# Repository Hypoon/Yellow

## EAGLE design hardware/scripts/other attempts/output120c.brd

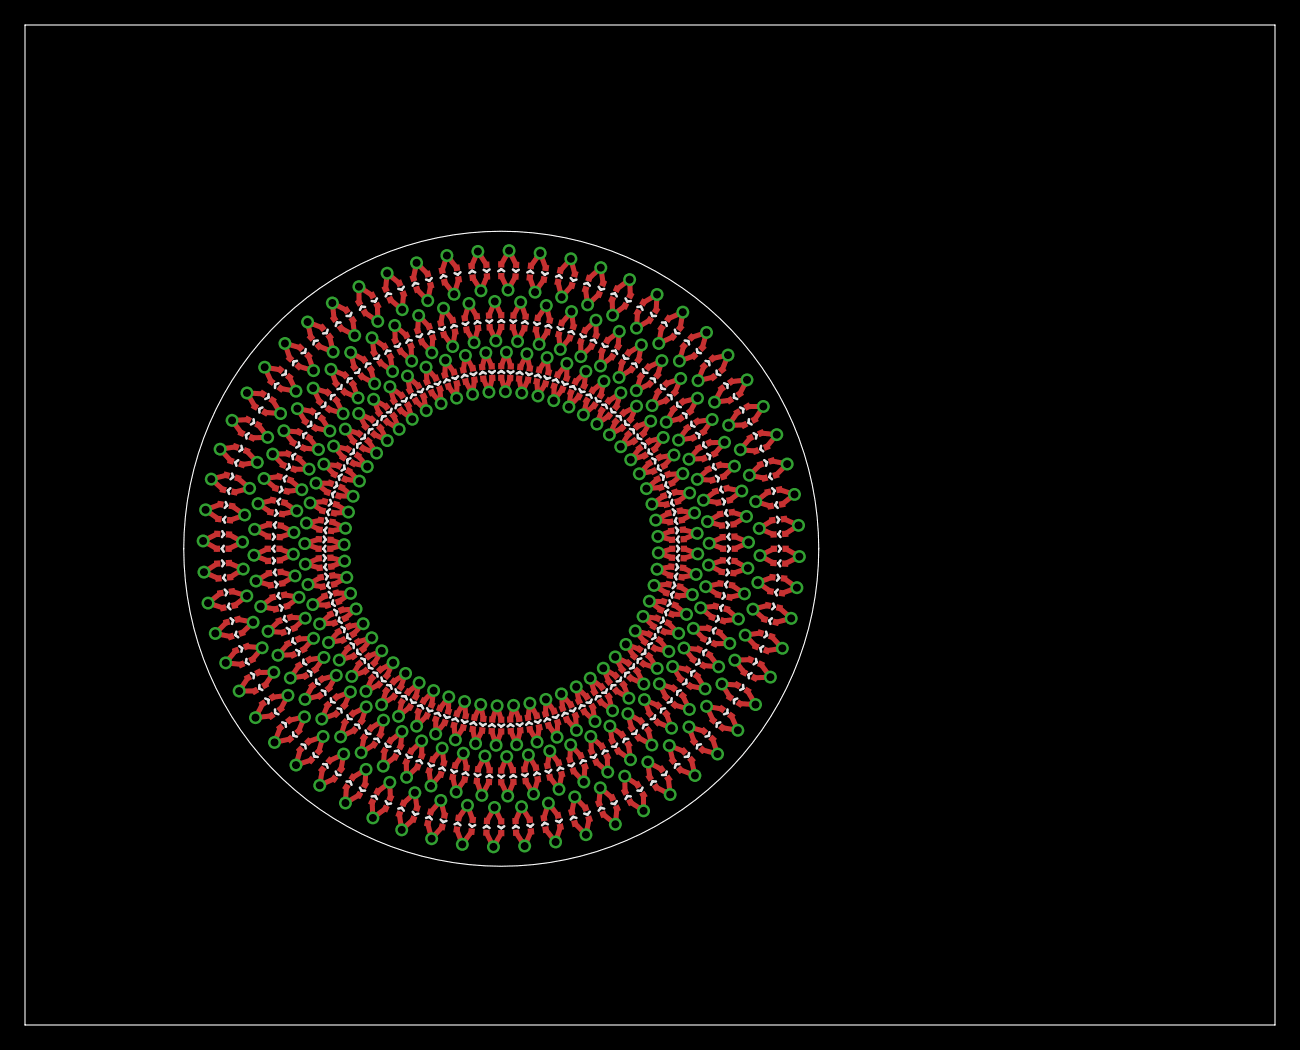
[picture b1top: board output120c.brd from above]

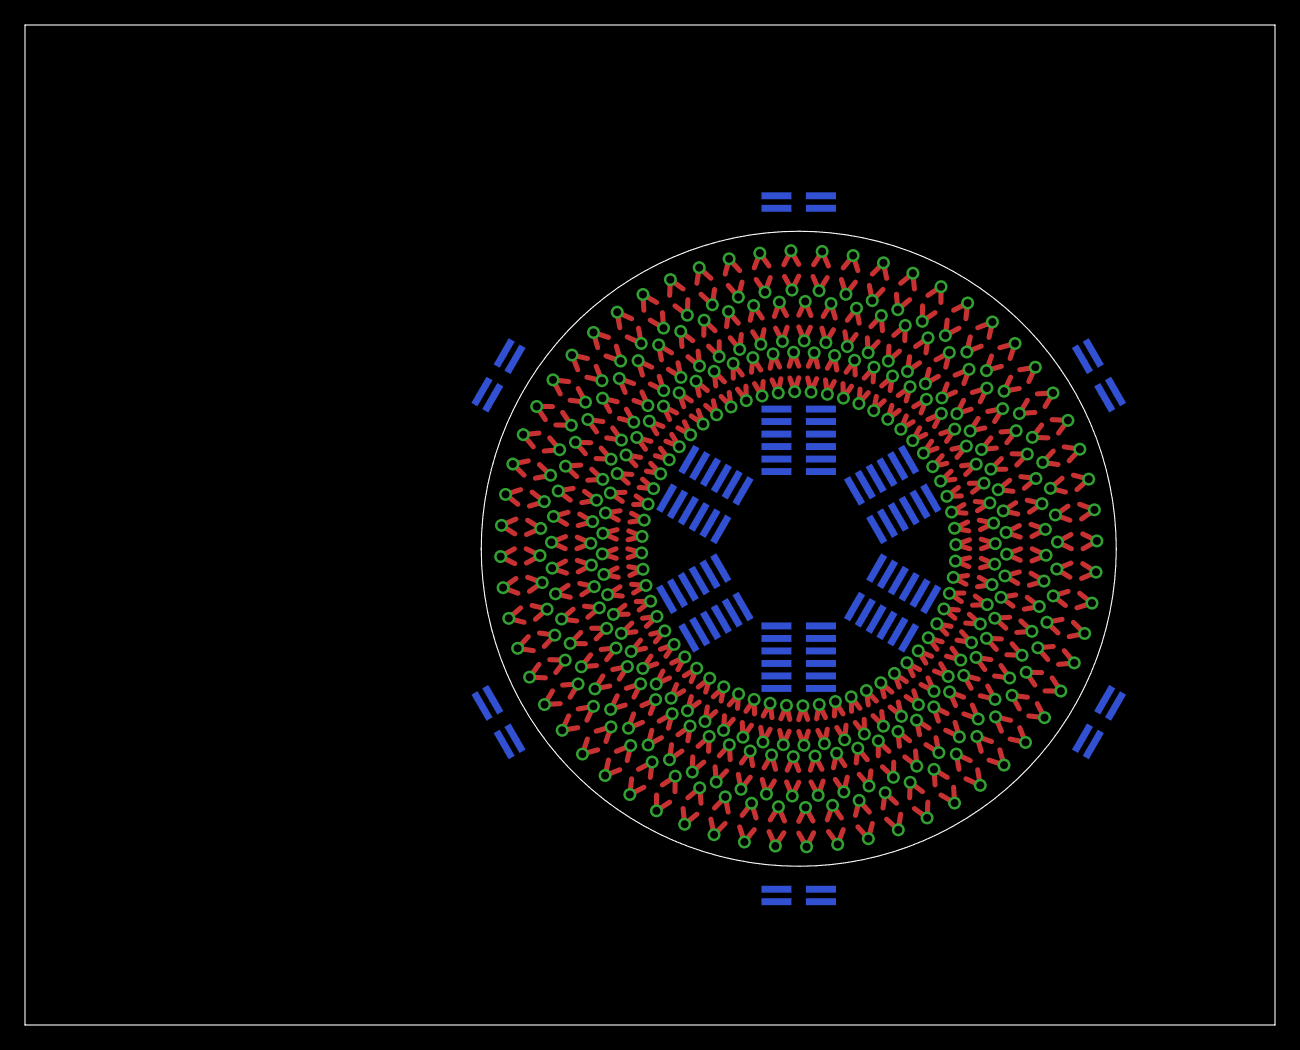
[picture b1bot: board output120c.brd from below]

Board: 2 copper layers, 100.0 x 80.0 mm, 378 parts (18 on the bottom side), 360 nets.

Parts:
H1, H2, H3, H4, H5, H6, H7, H8, H9, H10, H11, H12: 2X3; 3X2_1MM_SMD
H13, H14, H15, H16, H17, H18: 2X2; 2X2_1MM_SMD
LED1, LED2, LED3, LED4, LED5, LED6, LED7, LED8, LED9, LED10, LED11, LED12, LED13, LED14, LED15, LED16, LED17, LED18, LED19, LED20, LED21, LED22, LED23, LED24, LED25, LED26, LED27, LED28, LED29, LED30, LED31, LED32, LED33, LED34, LED35, LED36, LED37, LED38, LED39, LED40, LED41, LED42, LED43, LED44, LED45, LED46, LED47, LED48, LED49, LED50, LED51, LED52, LED53, LED54, LED55, LED56, LED57, LED58, LED59, LED60, LED61, LED62, LED63, LED64, LED65, LED66, LED67, LED68, LED69, LED70, LED71, LED72, LED73, LED74, LED75, LED76, LED77, LED78, LED79, LED80, LED81, LED82, LED83, LED84, LED85, LED86, LED87, LED88, LED89, LED90, LED91, LED92, LED93, LED94, LED95, LED96, LED97, LED98, LED99, LED100, LED101, LED102, LED103, LED104, LED105, LED106, LED107, LED108, LED109, LED110, LED111, LED112, LED113, LED114, LED115, LED116, LED117, LED118, LED119, LED120: RED; LED-0402
LED121, LED122, LED123, LED124, LED125, LED126, LED127, LED128, LED129, LED130, LED131, LED132, LED133, LED134, LED135, LED136, LED137, LED138, LED139, LED140, LED141, LED142, LED143, LED144, LED145, LED146, LED147, LED148, LED149, LED150, LED151, LED152, LED153, LED154, LED155, LED156, LED157, LED158, LED159, LED160, LED161, LED162, LED163, LED164, LED165, LED166, LED167, LED168, LED169, LED170, LED171, LED172, LED173, LED174, LED175, LED176, LED177, LED178, LED179, LED180, LED181, LED182, LED183, LED184, LED185, LED186, LED187, LED188, LED189, LED190, LED191, LED192, LED193, LED194, LED195, LED196, LED197, LED198, LED199, LED200, LED201, LED202, LED203, LED204, LED205, LED206, LED207, LED208, LED209, LED210, LED211, LED212, LED213, LED214, LED215, LED216, LED217, LED218, LED219, LED220, LED221, LED222, LED223, LED224, LED225, LED226, LED227, LED228, LED229, LED230, LED231, LED232, LED233, LED234, LED235, LED236, LED237, LED238, LED239, LED240: GREEN; LED-0402
LED241, LED242, LED243, LED244, LED245, LED246, LED247, LED248, LED249, LED250, LED251, LED252, LED253, LED254, LED255, LED256, LED257, LED258, LED259, LED260, LED261, LED262, LED263, LED264, LED265, LED266, LED267, LED268, LED269, LED270, LED271, LED272, LED273, LED274, LED275, LED276, LED277, LED278, LED279, LED280, LED281, LED282, LED283, LED284, LED285, LED286, LED287, LED288, LED289, LED290, LED291, LED292, LED293, LED294, LED295, LED296, LED297, LED298, LED299, LED300, LED301, LED302, LED303, LED304, LED305, LED306, LED307, LED308, LED309, LED310, LED311, LED312, LED313, LED314, LED315, LED316, LED317, LED318, LED319, LED320, LED321, LED322, LED323, LED324, LED325, LED326, LED327, LED328, LED329, LED330, LED331, LED332, LED333, LED334, LED335, LED336, LED337, LED338, LED339, LED340, LED341, LED342, LED343, LED344, LED345, LED346, LED347, LED348, LED349, LED350, LED351, LED352, LED353, LED354, LED355, LED356, LED357, LED358, LED359, LED360: BLUE; LED-0402

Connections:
unnamed: LED1.A, LED2.C
unnamed: LED3.A, LED4.C
unnamed: LED5.A, LED6.C
unnamed: LED7.A, LED8.C
unnamed: LED9.A, LED10.C
unnamed: LED11.A, LED12.C
unnamed: LED13.A, LED14.C
unnamed: LED15.A, LED16.C
unnamed: LED17.A, LED18.C
unnamed: LED19.A, LED20.C
unnamed: LED21.A, LED22.C
unnamed: LED23.A, LED24.C
unnamed: LED25.A, LED26.C
unnamed: LED27.A, LED28.C
unnamed: LED29.A, LED30.C
unnamed: LED31.A, LED32.C
unnamed: LED33.A, LED34.C
unnamed: LED35.A, LED36.C
unnamed: LED37.A, LED38.C
unnamed: LED39.A, LED40.C
unnamed: LED41.A, LED42.C
unnamed: LED43.A, LED44.C
unnamed: LED45.A, LED46.C
unnamed: LED47.A, LED48.C
unnamed: LED49.A, LED50.C
unnamed: LED51.A, LED52.C
unnamed: LED53.A, LED54.C
unnamed: LED55.A, LED56.C
unnamed: LED57.A, LED58.C
unnamed: LED59.A, LED60.C
unnamed: LED61.A, LED62.C
unnamed: LED63.A, LED64.C
unnamed: LED65.A, LED66.C
unnamed: LED67.A, LED68.C
unnamed: LED69.A, LED70.C
unnamed: LED71.A, LED72.C
unnamed: LED73.A, LED74.C
unnamed: LED75.A, LED76.C
unnamed: LED77.A, LED78.C
unnamed: LED79.A, LED80.C
unnamed: LED81.A, LED82.C
unnamed: LED83.A, LED84.C
unnamed: LED85.A, LED86.C
unnamed: LED87.A, LED88.C
unnamed: LED89.A, LED90.C
unnamed: LED91.A, LED92.C
unnamed: LED93.A, LED94.C
unnamed: LED95.A, LED96.C
unnamed: LED97.A, LED98.C
unnamed: LED99.A, LED100.C
unnamed: LED101.A, LED102.C
unnamed: LED103.A, LED104.C
unnamed: LED105.A, LED106.C
unnamed: LED107.A, LED108.C
unnamed: LED109.A, LED110.C
unnamed: LED111.A, LED112.C
unnamed: LED113.A, LED114.C
unnamed: LED115.A, LED116.C
unnamed: LED117.A, LED118.C
unnamed: LED119.A, LED120.C
unnamed: LED122.C, LED123.A
unnamed: LED124.C, LED125.A
unnamed: LED126.C, LED127.A
unnamed: LED128.C, LED129.A
unnamed: LED130.C, LED131.A
unnamed: LED132.C, LED133.A
unnamed: LED134.C, LED135.A
unnamed: LED136.C, LED137.A
unnamed: LED138.C, LED139.A
unnamed: LED140.C, LED141.A
unnamed: LED142.C, LED143.A
unnamed: LED144.C, LED145.A
unnamed: LED146.C, LED147.A
unnamed: LED148.C, LED149.A
unnamed: LED150.C, LED151.A
unnamed: LED152.C, LED153.A
unnamed: LED154.C, LED155.A
unnamed: LED156.C, LED157.A
unnamed: LED158.C, LED159.A
unnamed: LED160.C, LED161.A
unnamed: LED162.C, LED163.A
unnamed: LED164.C, LED165.A
unnamed: LED166.C, LED167.A
unnamed: LED168.C, LED169.A
unnamed: LED170.C, LED171.A
unnamed: LED172.C, LED173.A
unnamed: LED174.C, LED175.A
unnamed: LED176.C, LED177.A
unnamed: LED178.C, LED179.A
unnamed: LED180.C, LED181.A
unnamed: LED182.C, LED183.A
unnamed: LED184.C, LED185.A
unnamed: LED186.C, LED187.A
unnamed: LED188.C, LED189.A
unnamed: LED190.C, LED191.A
unnamed: LED192.C, LED193.A
unnamed: LED194.C, LED195.A
unnamed: LED196.C, LED197.A
unnamed: LED198.C, LED199.A
unnamed: LED200.C, LED201.A
unnamed: LED202.C, LED203.A
unnamed: LED204.C, LED205.A
unnamed: LED206.C, LED207.A
unnamed: LED208.C, LED209.A
unnamed: LED210.C, LED211.A
unnamed: LED212.C, LED213.A
unnamed: LED214.C, LED215.A
unnamed: LED216.C, LED217.A
unnamed: LED218.C, LED219.A
unnamed: LED220.C, LED221.A
unnamed: LED222.C, LED223.A
unnamed: LED224.C, LED225.A
unnamed: LED226.C, LED227.A
unnamed: LED228.C, LED229.A
unnamed: LED230.C, LED231.A
unnamed: LED232.C, LED233.A
unnamed: LED234.C, LED235.A
unnamed: LED236.C, LED237.A
unnamed: LED238.C, LED239.A
unnamed: LED121.A, LED240.C
unnamed: LED241.A, LED242.C
unnamed: LED243.A, LED244.C
unnamed: LED245.A, LED246.C
unnamed: LED247.A, LED248.C
unnamed: LED249.A, LED250.C
unnamed: LED251.A, LED252.C
unnamed: LED253.A, LED254.C
unnamed: LED255.A, LED256.C
unnamed: LED257.A, LED258.C
unnamed: LED259.A, LED260.C
unnamed: LED261.A, LED262.C
unnamed: LED263.A, LED264.C
unnamed: LED265.A, LED266.C
unnamed: LED267.A, LED268.C
unnamed: LED269.A, LED270.C
unnamed: LED271.A, LED272.C
unnamed: LED273.A, LED274.C
unnamed: LED275.A, LED276.C
unnamed: LED277.A, LED278.C
unnamed: LED279.A, LED280.C
unnamed: LED281.A, LED282.C
unnamed: LED283.A, LED284.C
unnamed: LED285.A, LED286.C
unnamed: LED287.A, LED288.C
unnamed: LED289.A, LED290.C
unnamed: LED291.A, LED292.C
unnamed: LED293.A, LED294.C
unnamed: LED295.A, LED296.C
unnamed: LED297.A, LED298.C
unnamed: LED299.A, LED300.C
unnamed: LED301.A, LED302.C
unnamed: LED303.A, LED304.C
unnamed: LED305.A, LED306.C
unnamed: LED307.A, LED308.C
unnamed: LED309.A, LED310.C
unnamed: LED311.A, LED312.C
unnamed: LED313.A, LED314.C
unnamed: LED315.A, LED316.C
unnamed: LED317.A, LED318.C
unnamed: LED319.A, LED320.C
unnamed: LED321.A, LED322.C
unnamed: LED323.A, LED324.C
unnamed: LED325.A, LED326.C
unnamed: LED327.A, LED328.C
unnamed: LED329.A, LED330.C
unnamed: LED331.A, LED332.C
unnamed: LED333.A, LED334.C
unnamed: LED335.A, LED336.C
unnamed: LED337.A, LED338.C
unnamed: LED339.A, LED340.C
unnamed: LED341.A, LED342.C
unnamed: LED343.A, LED344.C
unnamed: LED345.A, LED346.C
unnamed: LED347.A, LED348.C
unnamed: LED349.A, LED350.C
unnamed: LED351.A, LED352.C
unnamed: LED353.A, LED354.C
unnamed: LED355.A, LED356.C
unnamed: LED357.A, LED358.C
unnamed: LED359.A, LED360.C
unnamed: LED1.C, LED2.A
unnamed: LED3.C, LED4.A
unnamed: LED5.C, LED6.A
unnamed: LED7.C, LED8.A
unnamed: LED9.C, LED10.A
unnamed: LED11.C, LED12.A
unnamed: LED13.C, LED14.A
unnamed: LED15.C, LED16.A
unnamed: LED17.C, LED18.A
unnamed: LED19.C, LED20.A
unnamed: LED21.C, LED22.A
unnamed: LED23.C, LED24.A
unnamed: LED25.C, LED26.A
unnamed: LED27.C, LED28.A
unnamed: LED29.C, LED30.A
unnamed: LED31.C, LED32.A
unnamed: LED33.C, LED34.A
unnamed: LED35.C, LED36.A
unnamed: LED37.C, LED38.A
unnamed: LED39.C, LED40.A
unnamed: LED41.C, LED42.A
unnamed: LED43.C, LED44.A
unnamed: LED45.C, LED46.A
unnamed: LED47.C, LED48.A
unnamed: LED49.C, LED50.A
unnamed: LED51.C, LED52.A
unnamed: LED53.C, LED54.A
unnamed: LED55.C, LED56.A
unnamed: LED57.C, LED58.A
unnamed: LED59.C, LED60.A
unnamed: LED61.C, LED62.A
unnamed: LED63.C, LED64.A
unnamed: LED65.C, LED66.A
unnamed: LED67.C, LED68.A
unnamed: LED69.C, LED70.A
unnamed: LED71.C, LED72.A
unnamed: LED73.C, LED74.A
unnamed: LED75.C, LED76.A
unnamed: LED77.C, LED78.A
unnamed: LED79.C, LED80.A
unnamed: LED81.C, LED82.A
unnamed: LED83.C, LED84.A
unnamed: LED85.C, LED86.A
unnamed: LED87.C, LED88.A
unnamed: LED89.C, LED90.A
unnamed: LED91.C, LED92.A
unnamed: LED93.C, LED94.A
unnamed: LED95.C, LED96.A
unnamed: LED97.C, LED98.A
unnamed: LED99.C, LED100.A
unnamed: LED101.C, LED102.A
unnamed: LED103.C, LED104.A
unnamed: LED105.C, LED106.A
unnamed: LED107.C, LED108.A
unnamed: LED109.C, LED110.A
unnamed: LED111.C, LED112.A
unnamed: LED113.C, LED114.A
unnamed: LED115.C, LED116.A
unnamed: LED117.C, LED118.A
unnamed: LED119.C, LED120.A
unnamed: LED122.A, LED123.C
unnamed: LED124.A, LED125.C
unnamed: LED126.A, LED127.C
unnamed: LED128.A, LED129.C
unnamed: LED130.A, LED131.C
unnamed: LED132.A, LED133.C
unnamed: LED134.A, LED135.C
unnamed: LED136.A, LED137.C
unnamed: LED138.A, LED139.C
unnamed: LED140.A, LED141.C
unnamed: LED142.A, LED143.C
unnamed: LED144.A, LED145.C
unnamed: LED146.A, LED147.C
unnamed: LED148.A, LED149.C
unnamed: LED150.A, LED151.C
unnamed: LED152.A, LED153.C
unnamed: LED154.A, LED155.C
unnamed: LED156.A, LED157.C
unnamed: LED158.A, LED159.C
unnamed: LED160.A, LED161.C
unnamed: LED162.A, LED163.C
unnamed: LED164.A, LED165.C
unnamed: LED166.A, LED167.C
unnamed: LED168.A, LED169.C
unnamed: LED170.A, LED171.C
unnamed: LED172.A, LED173.C
unnamed: LED174.A, LED175.C
unnamed: LED176.A, LED177.C
unnamed: LED178.A, LED179.C
unnamed: LED180.A, LED181.C
unnamed: LED182.A, LED183.C
unnamed: LED184.A, LED185.C
unnamed: LED186.A, LED187.C
unnamed: LED188.A, LED189.C
unnamed: LED190.A, LED191.C
unnamed: LED192.A, LED193.C
unnamed: LED194.A, LED195.C
unnamed: LED196.A, LED197.C
unnamed: LED198.A, LED199.C
unnamed: LED200.A, LED201.C
unnamed: LED202.A, LED203.C
unnamed: LED204.A, LED205.C
unnamed: LED206.A, LED207.C
unnamed: LED208.A, LED209.C
unnamed: LED210.A, LED211.C
unnamed: LED212.A, LED213.C
unnamed: LED214.A, LED215.C
unnamed: LED216.A, LED217.C
unnamed: LED218.A, LED219.C
unnamed: LED220.A, LED221.C
unnamed: LED222.A, LED223.C
unnamed: LED224.A, LED225.C
unnamed: LED226.A, LED227.C
unnamed: LED228.A, LED229.C
unnamed: LED230.A, LED231.C
unnamed: LED232.A, LED233.C
unnamed: LED234.A, LED235.C
unnamed: LED236.A, LED237.C
unnamed: LED238.A, LED239.C
unnamed: LED121.C, LED240.A
unnamed: LED241.C, LED242.A
unnamed: LED243.C, LED244.A
unnamed: LED245.C, LED246.A
unnamed: LED247.C, LED248.A
unnamed: LED249.C, LED250.A
unnamed: LED251.C, LED252.A
unnamed: LED253.C, LED254.A
unnamed: LED255.C, LED256.A
unnamed: LED257.C, LED258.A
unnamed: LED259.C, LED260.A
unnamed: LED261.C, LED262.A
unnamed: LED263.C, LED264.A
unnamed: LED265.C, LED266.A
unnamed: LED267.C, LED268.A
unnamed: LED269.C, LED270.A
unnamed: LED271.C, LED272.A
unnamed: LED273.C, LED274.A
unnamed: LED275.C, LED276.A
unnamed: LED277.C, LED278.A
unnamed: LED279.C, LED280.A
unnamed: LED281.C, LED282.A
unnamed: LED283.C, LED284.A
unnamed: LED285.C, LED286.A
unnamed: LED287.C, LED288.A
unnamed: LED289.C, LED290.A
unnamed: LED291.C, LED292.A
unnamed: LED293.C, LED294.A
unnamed: LED295.C, LED296.A
unnamed: LED297.C, LED298.A
unnamed: LED299.C, LED300.A
unnamed: LED301.C, LED302.A
unnamed: LED303.C, LED304.A
unnamed: LED305.C, LED306.A
unnamed: LED307.C, LED308.A
unnamed: LED309.C, LED310.A
unnamed: LED311.C, LED312.A
unnamed: LED313.C, LED314.A
unnamed: LED315.C, LED316.A
unnamed: LED317.C, LED318.A
unnamed: LED319.C, LED320.A
unnamed: LED321.C, LED322.A
unnamed: LED323.C, LED324.A
unnamed: LED325.C, LED326.A
unnamed: LED327.C, LED328.A
unnamed: LED329.C, LED330.A
unnamed: LED331.C, LED332.A
unnamed: LED333.C, LED334.A
unnamed: LED335.C, LED336.A
unnamed: LED337.C, LED338.A
unnamed: LED339.C, LED340.A
unnamed: LED341.C, LED342.A
unnamed: LED343.C, LED344.A
unnamed: LED345.C, LED346.A
unnamed: LED347.C, LED348.A
unnamed: LED349.C, LED350.A
unnamed: LED351.C, LED352.A
unnamed: LED353.C, LED354.A
unnamed: LED355.C, LED356.A
unnamed: LED357.C, LED358.A
unnamed: LED359.C, LED360.A

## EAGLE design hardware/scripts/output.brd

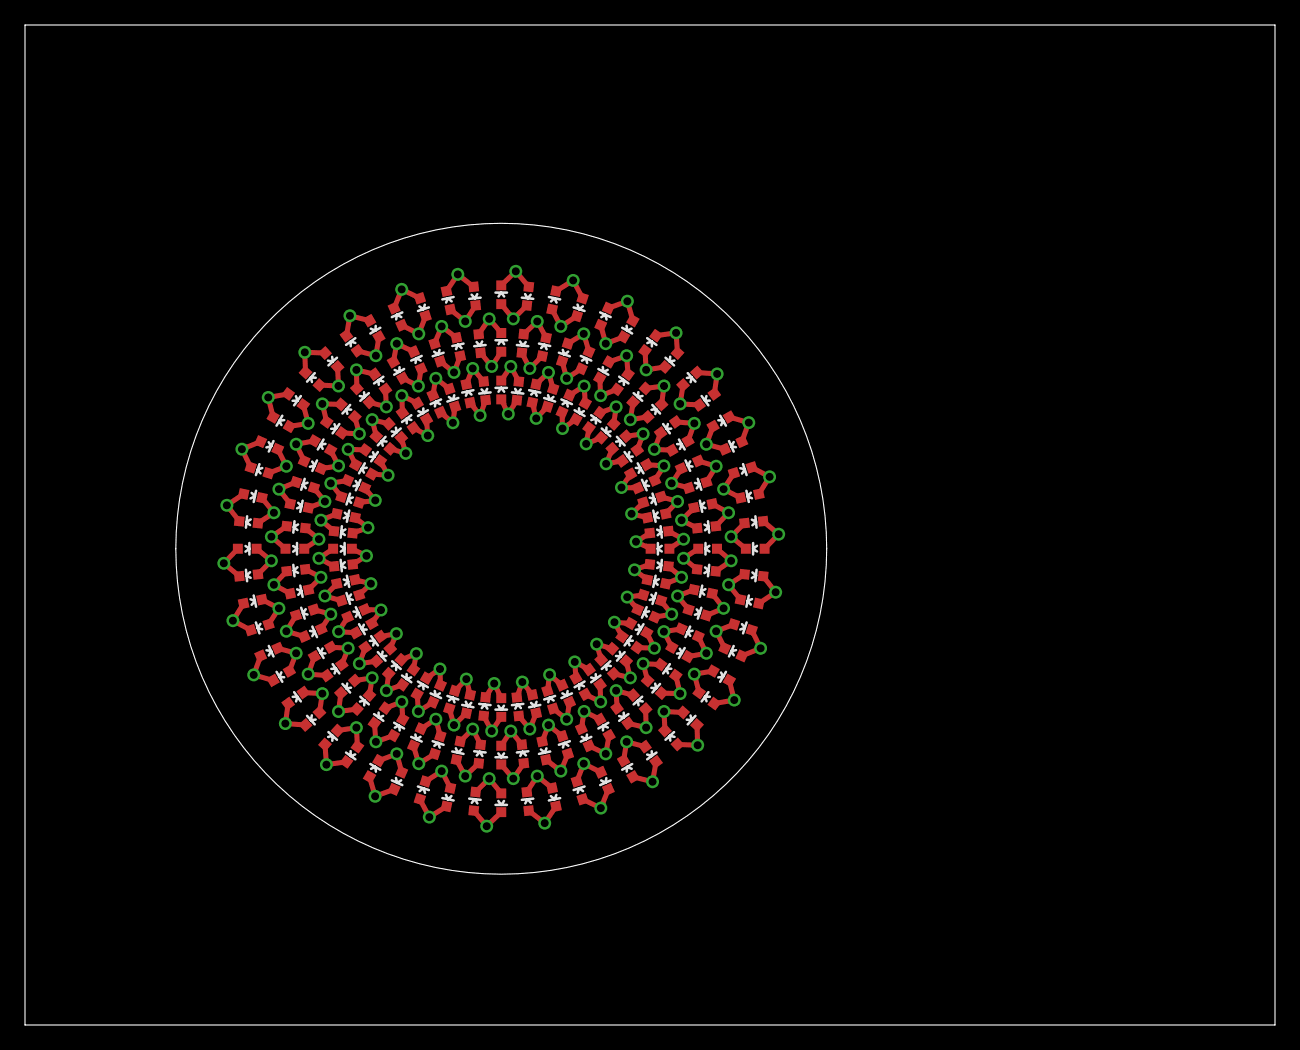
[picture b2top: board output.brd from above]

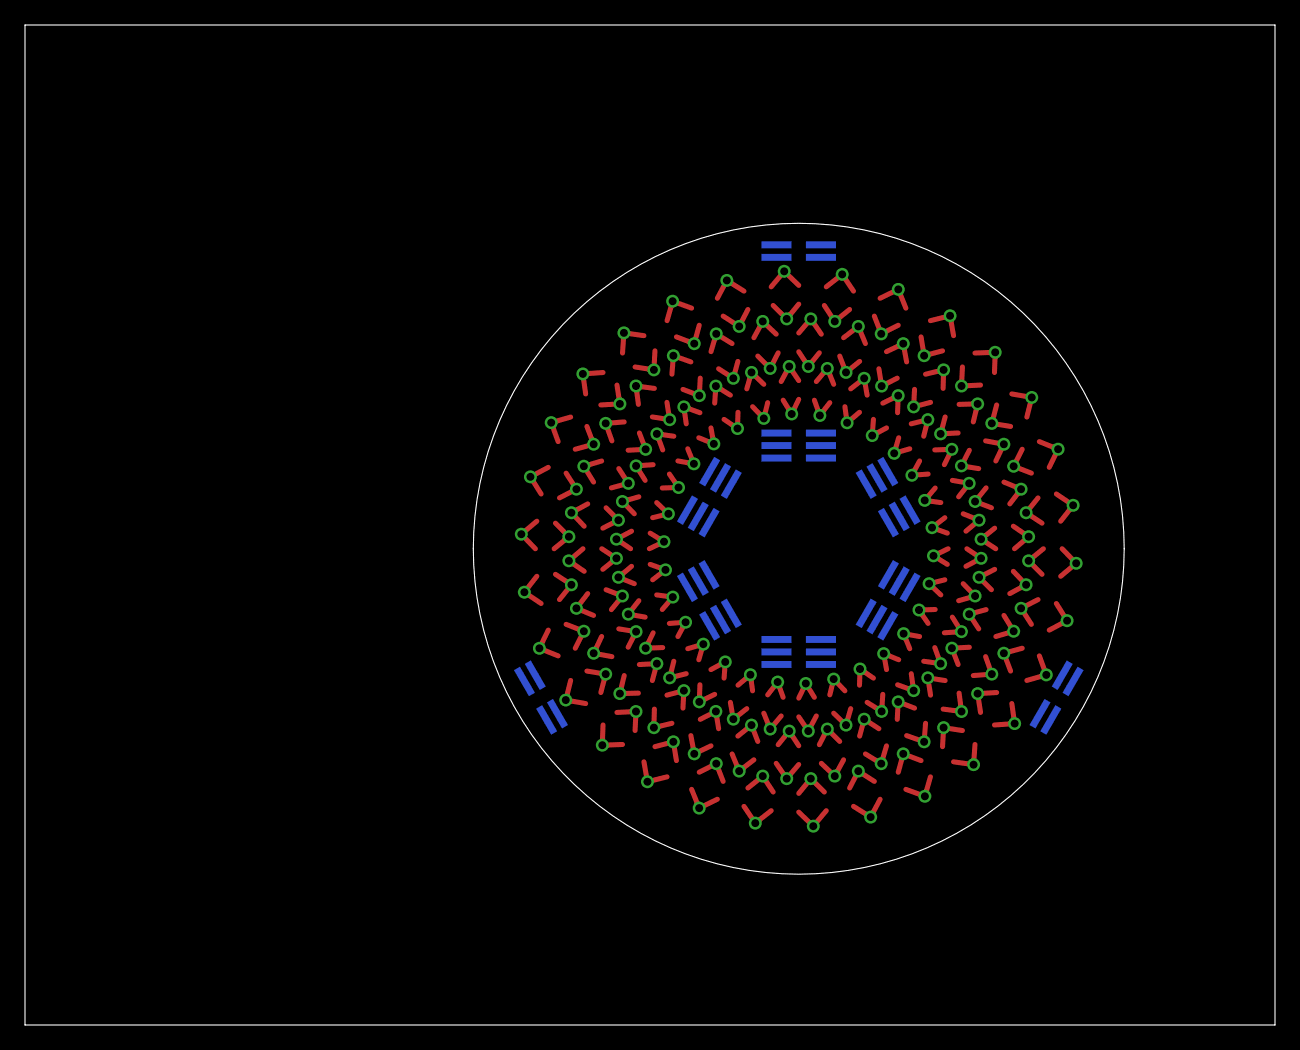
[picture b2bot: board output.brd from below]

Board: 2 copper layers, 100.0 x 80.0 mm, 189 parts (9 on the bottom side), 180 nets.

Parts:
H1, H2, H3, H4, H5, H6: 2X3; 3X2_1MM_SMD
H7, H8, H9: 2X2; 2X2_1MM_SMD
LED1, LED2, LED3, LED4, LED5, LED6, LED7, LED8, LED9, LED10, LED11, LED12, LED13, LED14, LED15, LED16, LED17, LED18, LED19, LED20, LED21, LED22, LED23, LED24, LED25, LED26, LED27, LED28, LED29, LED30, LED31, LED32, LED33, LED34, LED35, LED36, LED37, LED38, LED39, LED40, LED41, LED42, LED43, LED44, LED45, LED46, LED47, LED48, LED49, LED50, LED51, LED52, LED53, LED54, LED55, LED56, LED57, LED58, LED59, LED60: RED; LED-0603
LED61, LED62, LED63, LED64, LED65, LED66, LED67, LED68, LED69, LED70, LED71, LED72, LED73, LED74, LED75, LED76, LED77, LED78, LED79, LED80, LED81, LED82, LED83, LED84, LED85, LED86, LED87, LED88, LED89, LED90, LED91, LED92, LED93, LED94, LED95, LED96, LED97, LED98, LED99, LED100, LED101, LED102, LED103, LED104, LED105, LED106, LED107, LED108, LED109, LED110, LED111, LED112, LED113, LED114, LED115, LED116, LED117, LED118, LED119, LED120: GREEN; LED-0603
LED121, LED122, LED123, LED124, LED125, LED126, LED127, LED128, LED129, LED130, LED131, LED132, LED133, LED134, LED135, LED136, LED137, LED138, LED139, LED140, LED141, LED142, LED143, LED144, LED145, LED146, LED147, LED148, LED149, LED150, LED151, LED152, LED153, LED154, LED155, LED156, LED157, LED158, LED159, LED160, LED161, LED162, LED163, LED164, LED165, LED166, LED167, LED168, LED169, LED170, LED171, LED172, LED173, LED174, LED175, LED176, LED177, LED178, LED179, LED180: BLUE; LED-0603

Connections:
unnamed: LED1.A, LED2.C
unnamed: LED3.A, LED4.C
unnamed: LED5.A, LED6.C
unnamed: LED7.A, LED8.C
unnamed: LED9.A, LED10.C
unnamed: LED11.A, LED12.C
unnamed: LED13.A, LED14.C
unnamed: LED15.A, LED16.C
unnamed: LED17.A, LED18.C
unnamed: LED19.A, LED20.C
unnamed: LED21.A, LED22.C
unnamed: LED23.A, LED24.C
unnamed: LED25.A, LED26.C
unnamed: LED27.A, LED28.C
unnamed: LED29.A, LED30.C
unnamed: LED31.A, LED32.C
unnamed: LED33.A, LED34.C
unnamed: LED35.A, LED36.C
unnamed: LED37.A, LED38.C
unnamed: LED39.A, LED40.C
unnamed: LED41.A, LED42.C
unnamed: LED43.A, LED44.C
unnamed: LED45.A, LED46.C
unnamed: LED47.A, LED48.C
unnamed: LED49.A, LED50.C
unnamed: LED51.A, LED52.C
unnamed: LED53.A, LED54.C
unnamed: LED55.A, LED56.C
unnamed: LED57.A, LED58.C
unnamed: LED59.A, LED60.C
unnamed: LED62.C, LED63.A
unnamed: LED64.C, LED65.A
unnamed: LED66.C, LED67.A
unnamed: LED68.C, LED69.A
unnamed: LED70.C, LED71.A
unnamed: LED72.C, LED73.A
unnamed: LED74.C, LED75.A
unnamed: LED76.C, LED77.A
unnamed: LED78.C, LED79.A
unnamed: LED80.C, LED81.A
unnamed: LED82.C, LED83.A
unnamed: LED84.C, LED85.A
unnamed: LED86.C, LED87.A
unnamed: LED88.C, LED89.A
unnamed: LED90.C, LED91.A
unnamed: LED92.C, LED93.A
unnamed: LED94.C, LED95.A
unnamed: LED96.C, LED97.A
unnamed: LED98.C, LED99.A
unnamed: LED100.C, LED101.A
unnamed: LED102.C, LED103.A
unnamed: LED104.C, LED105.A
unnamed: LED106.C, LED107.A
unnamed: LED108.C, LED109.A
unnamed: LED110.C, LED111.A
unnamed: LED112.C, LED113.A
unnamed: LED114.C, LED115.A
unnamed: LED116.C, LED117.A
unnamed: LED118.C, LED119.A
unnamed: LED61.A, LED120.C
unnamed: LED121.A, LED122.C
unnamed: LED123.A, LED124.C
unnamed: LED125.A, LED126.C
unnamed: LED127.A, LED128.C
unnamed: LED129.A, LED130.C
unnamed: LED131.A, LED132.C
unnamed: LED133.A, LED134.C
unnamed: LED135.A, LED136.C
unnamed: LED137.A, LED138.C
unnamed: LED139.A, LED140.C
unnamed: LED141.A, LED142.C
unnamed: LED143.A, LED144.C
unnamed: LED145.A, LED146.C
unnamed: LED147.A, LED148.C
unnamed: LED149.A, LED150.C
unnamed: LED151.A, LED152.C
unnamed: LED153.A, LED154.C
unnamed: LED155.A, LED156.C
unnamed: LED157.A, LED158.C
unnamed: LED159.A, LED160.C
unnamed: LED161.A, LED162.C
unnamed: LED163.A, LED164.C
unnamed: LED165.A, LED166.C
unnamed: LED167.A, LED168.C
unnamed: LED169.A, LED170.C
unnamed: LED171.A, LED172.C
unnamed: LED173.A, LED174.C
unnamed: LED175.A, LED176.C
unnamed: LED177.A, LED178.C
unnamed: LED179.A, LED180.C
unnamed: LED1.C, LED2.A
unnamed: LED3.C, LED4.A
unnamed: LED5.C, LED6.A
unnamed: LED7.C, LED8.A
unnamed: LED9.C, LED10.A
unnamed: LED11.C, LED12.A
unnamed: LED13.C, LED14.A
unnamed: LED15.C, LED16.A
unnamed: LED17.C, LED18.A
unnamed: LED19.C, LED20.A
unnamed: LED21.C, LED22.A
unnamed: LED23.C, LED24.A
unnamed: LED25.C, LED26.A
unnamed: LED27.C, LED28.A
unnamed: LED29.C, LED30.A
unnamed: LED31.C, LED32.A
unnamed: LED33.C, LED34.A
unnamed: LED35.C, LED36.A
unnamed: LED37.C, LED38.A
unnamed: LED39.C, LED40.A
unnamed: LED41.C, LED42.A
unnamed: LED43.C, LED44.A
unnamed: LED45.C, LED46.A
unnamed: LED47.C, LED48.A
unnamed: LED49.C, LED50.A
unnamed: LED51.C, LED52.A
unnamed: LED53.C, LED54.A
unnamed: LED55.C, LED56.A
unnamed: LED57.C, LED58.A
unnamed: LED59.C, LED60.A
unnamed: LED62.A, LED63.C
unnamed: LED64.A, LED65.C
unnamed: LED66.A, LED67.C
unnamed: LED68.A, LED69.C
unnamed: LED70.A, LED71.C
unnamed: LED72.A, LED73.C
unnamed: LED74.A, LED75.C
unnamed: LED76.A, LED77.C
unnamed: LED78.A, LED79.C
unnamed: LED80.A, LED81.C
unnamed: LED82.A, LED83.C
unnamed: LED84.A, LED85.C
unnamed: LED86.A, LED87.C
unnamed: LED88.A, LED89.C
unnamed: LED90.A, LED91.C
unnamed: LED92.A, LED93.C
unnamed: LED94.A, LED95.C
unnamed: LED96.A, LED97.C
unnamed: LED98.A, LED99.C
unnamed: LED100.A, LED101.C
unnamed: LED102.A, LED103.C
unnamed: LED104.A, LED105.C
unnamed: LED106.A, LED107.C
unnamed: LED108.A, LED109.C
unnamed: LED110.A, LED111.C
unnamed: LED112.A, LED113.C
unnamed: LED114.A, LED115.C
unnamed: LED116.A, LED117.C
unnamed: LED118.A, LED119.C
unnamed: LED61.C, LED120.A
unnamed: LED121.C, LED122.A
unnamed: LED123.C, LED124.A
unnamed: LED125.C, LED126.A
unnamed: LED127.C, LED128.A
unnamed: LED129.C, LED130.A
unnamed: LED131.C, LED132.A
unnamed: LED133.C, LED134.A
unnamed: LED135.C, LED136.A
unnamed: LED137.C, LED138.A
unnamed: LED139.C, LED140.A
unnamed: LED141.C, LED142.A
unnamed: LED143.C, LED144.A
unnamed: LED145.C, LED146.A
unnamed: LED147.C, LED148.A
unnamed: LED149.C, LED150.A
unnamed: LED151.C, LED152.A
unnamed: LED153.C, LED154.A
unnamed: LED155.C, LED156.A
unnamed: LED157.C, LED158.A
unnamed: LED159.C, LED160.A
unnamed: LED161.C, LED162.A
unnamed: LED163.C, LED164.A
unnamed: LED165.C, LED166.A
unnamed: LED167.C, LED168.A
unnamed: LED169.C, LED170.A
unnamed: LED171.C, LED172.A
unnamed: LED173.C, LED174.A
unnamed: LED175.C, LED176.A
unnamed: LED177.C, LED178.A
unnamed: LED179.C, LED180.A
